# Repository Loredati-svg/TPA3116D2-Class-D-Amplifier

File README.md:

<h1 align="center">🔊 Class-D Stereo Audio Amplifier</h1>

An open-source stereo **Class-D** audio amplifier with a **USB-C digital input**, analog **bass / treble tone control** and a **volume knob**, built around the Texas Instruments **TPA3116D2** and designed in **KiCad 10.0**.

Plug a phone or a PC into the USB-C port: the board shows up as a standard USB sound card (no drivers needed) and drives a pair of passive bookshelf speakers (4–8 Ω) from a single **24 V DC** supply.

---

> 🛠️ **Project Status: Active Development (v1)**
> The v1 schematic is being finalized; PCB layout comes next. Suggestions and feedback are welcome!

> 📶 **About Bluetooth**
> Bluetooth support is currently **on hold**. It will be reintegrated in a future hardware revision, once the v1 board (USB-C, without Bluetooth) has been built and validated.

---

## Libraries

This project uses the shared KiCad libraries from L2-Hardware.

1. Clone the library repository **in the same parent folder as your project folders**, so that it sits next to them:

```bash
   git clone https://github.com/L2-Hardware/Kicad_Libs
```

   Expected folder structure:

```
   Kicad/
   ├── Kicad_Libs/
   ├── Project1/
   └── Project2/
   └── etc...
```
---

2. Inside the project folder, run the `bring_libs.bat` script to import the libraries into the project.

## 📋 Table of Contents
- [Technical Specifications](#-technical-specifications)
- [Signal Chain](#-signal-chain)
- [Circuit Blocks](#-circuit-blocks)
- [Gain Structure](#-gain-structure)
- [Repository Structure](#-repository-structure)
- [Manufacturing](#-manufacturing)
- [Roadmap](#-roadmap)
- [License](#-license)

---

## ⚡ Technical Specifications

| Parameter | Value |
| :--- | :--- |
| **Supply voltage** | 24 V DC (3–5 A recommended), 5.5 × 2.1 mm barrel jack |
| **Audio input** | USB-C (USB 2.0 Full-Speed, USB Audio Class 1.0), 16-bit / up to 48 kHz |
| **DAC** | Texas Instruments **PCM2704C** |
| **Tone control** | Active Baxandall – bass and treble, about ±12 dB |
| **Amplifier IC** | Texas Instruments **TPA3116D2** (stereo BTL, Master mode, 26 dB) |
| **Output power** | ≈ 2 × 40 W into 4 Ω (clean), up to 2 × 50 W at 10 % THD |
| **Speaker load** | 4–8 Ω passive speakers |
| **Speaker outputs** | Phoenix Contact MKDS 1,5/2-5,08 screw terminals |
| **Controls** | Bass, Treble, Volume (dual-gang potentiometers) |
| **PCB** | 4 layers, FR-4, 1.6 mm, 1 oz copper |

---

## 🔗 Signal Chain

```mermaid
flowchart LR
    A[Phone / PC<br/>USB-C] --> B[PCM2704C<br/>USB Audio DAC]
    B --> C[Baxandall tone control<br/>OPA1678 · Bass / Treble]
    C --> D[Volume<br/>dual log pot]
    D --> E[TPA3116D2<br/>26 dB]
    E --> F[LC filter]
    F --> G[Speakers<br/>4–8 Ω]
```

---

## 🧩 Circuit Blocks

### USB-C input and DAC
- USB 2.0 Type-C receptacle with **5.1 kΩ** pull-downs on CC1/CC2 (device / UFP), so the phone acts as host and supplies VBUS
- **USBLC6-2SC6** ESD protection on D+, D− and VBUS
- **PCM2704C** bus-powered from VBUS: USB Audio Class 1.0, driverless on Android, iOS, Windows, macOS and Linux
- 12 MHz crystal, 22 Ω series resistors and 1.5 kΩ pull-up on D+
- AC-coupled line outputs (10 µF + 47 kΩ)

### Tone control
- Active **Baxandall** network (one per channel) around a TI **OPA1678** (dual, rail-to-rail output, low noise)
- **Bass:** shelf centred around ≈ 50 Hz, tuned for deep 808-style bass
- **Treble:** ≈ 8–10 kHz, mainly to tame harsh highs
- Unity gain with the knobs centred

### Volume
- Dual-gang **A10K** logarithmic potentiometer
- Placed **after** the tone stage, so it also attenuates op-amp noise at low listening levels

### Analog supply
- **L78L12** LDO: 24 V → 12 V for the op-amp
- **VREF = 6 V** virtual ground (100 kΩ / 100 kΩ divider + 10 µF) for single-supply operation

### Power amplifier (TPA3116D2)
- **Gain / mode:** 20 kΩ to GND and 100 kΩ to GVDD on `GAIN/SLV` → Master mode, 26 dB, 30 kΩ input impedance
- **Inputs:** single-ended, negative inputs AC-grounded through capacitors matching the positive ones (3.3 µF)
- **Modulation:** BD mode, 400 kHz switching, no power limit
- **PVCC decoupling:** 1 nF + 100 nF ceramic + 220 µF + 470 µF low-ESR bulk on each side of the IC
- **Output filter:** 10 µH / 680 nF LC filter + RC snubbers for EMI
- **Protection:** `FAULTZ` tied to `SDZ` for automatic recovery after a fault
- **Thermal:** the DAD package has its **PowerPAD on top**, so a heatsink must be mounted on the IC

### Anti-pop
- The PCM2704C `SSPND` signal (high when USB audio is active) drives a **2N7002** inverter on the TPA3116D2 `MUTE` pin
- RC network on `MUTE` (100 kΩ + 4.7 µF): unmute ≈ 1 s after the DAC becomes active, mute within ≈ 0.1 s when the phone is unplugged, slew rate within datasheet limits
- RC delay on `SDZ` (100 kΩ + 10 µF) keeps the amplifier in shutdown while the supplies settle at power-up

### Front-panel controls

| Knob | Part | Function |
| :--- | :--- | :--- |
| **Bass** | B100K dual-gang (RV1) | Low-frequency boost / cut |
| **Treble** | B100K dual-gang (RV2) | High-frequency boost / cut |
| **Volume** | A10K dual-gang (RV3) | Master volume |

---

## 📊 Gain Structure

The gain chain is chosen so that **full volume reaches maximum clean power without clipping**, and the op-amp keeps headroom even with the bass knob fully up.

| Stage | Gain | Level at full scale |
| :--- | :--- | :--- |
| PCM2704C output | – | 0.64 Vrms |
| Tone control (flat) | ×1 (0 dB) | 0.64 Vrms |
| Volume (max) | ×1 | 0.64 Vrms |
| TPA3116D2 | ×20 (26 dB) | ≈ 12.8 Vrms → ≈ 40 W into 4 Ω |

Worst case (full-scale track, +12 dB bass boost): the OPA1678 output swings ≈ 7.2 Vpp around 6 V, well inside its 12 V rail-to-rail range. If the amplifier clips, it happens **after** the volume knob, so turning the volume down removes it.

---

## 📁 Repository Structure

```
Class-D-Bluetooth-5.0-Stereo-Audio-Amplifier/
├── KiCad_Project/
│   ├── Audio_Amp_v1/          # v1 – USB-C DAC + tone control (schematic + PCB)
│   └── Fabrication_files/     # Gerber, drill, BOM and CPL (coming soon)
├── libs/                           # Project-specific symbols, footprints and 3D models
└── README.md
```

### Schematic sheets

| Sheet | Content |
| :--- | :--- |
| `USB_DAC` | USB-C, ESD protection, PCM2704C, crystal, L78L12, power input, speaker terminals, anti-pop driver |
| `Tone_Volume_control` | OPA1678, VREF, Baxandall networks (L/R), volume potentiometer |
| `Power_Amplifier` | TPA3116D2, gain setting, PVCC decoupling, LC output filter, EMI snubbers |

---

## 🏭 Manufacturing

The board is designed to be manufactured by **JLCPCB** and assembled by hand (stencil + hot plate / hot air for SMD parts, soldering iron for through-hole parts).

| Option | Value |
| :--- | :--- |
| Layers | 4 |
| Thickness | 1.6 mm |
| Copper | 1 oz |
| Gerber export | Protel extensions, no X2 attributes |
| Drill | Excellon, mm, PTH + NPTH merged |
| Stencil | Top side only |

---

## 🗺️ Roadmap

**v1 – USB-C DAC (current)**
- [x] USB-C input and PCM2704C DAC
- [x] Baxandall tone control and volume
- [x] TPA3116D2 power stage
- [x] Anti-pop circuit
- [x] ERC and schematic review
- [x] PCB layout and DRC
- [ ] Fabrication, assembly and bring-up
- [ ] Measurements (frequency response, THD+N, noise)
- [ ] Enclosure and front panel

**Future**
- [ ] Bluetooth input (reintegrated once v1 is validated)

---

## 📜 License

This hardware project is released under the **CERN Open Hardware Licence Permissive v2 ([CERN-OHL-P v2](https://ohwr.org/cernohl))**.

<p align="center">Designed by <b>LOREDATI Circuits</b></p>

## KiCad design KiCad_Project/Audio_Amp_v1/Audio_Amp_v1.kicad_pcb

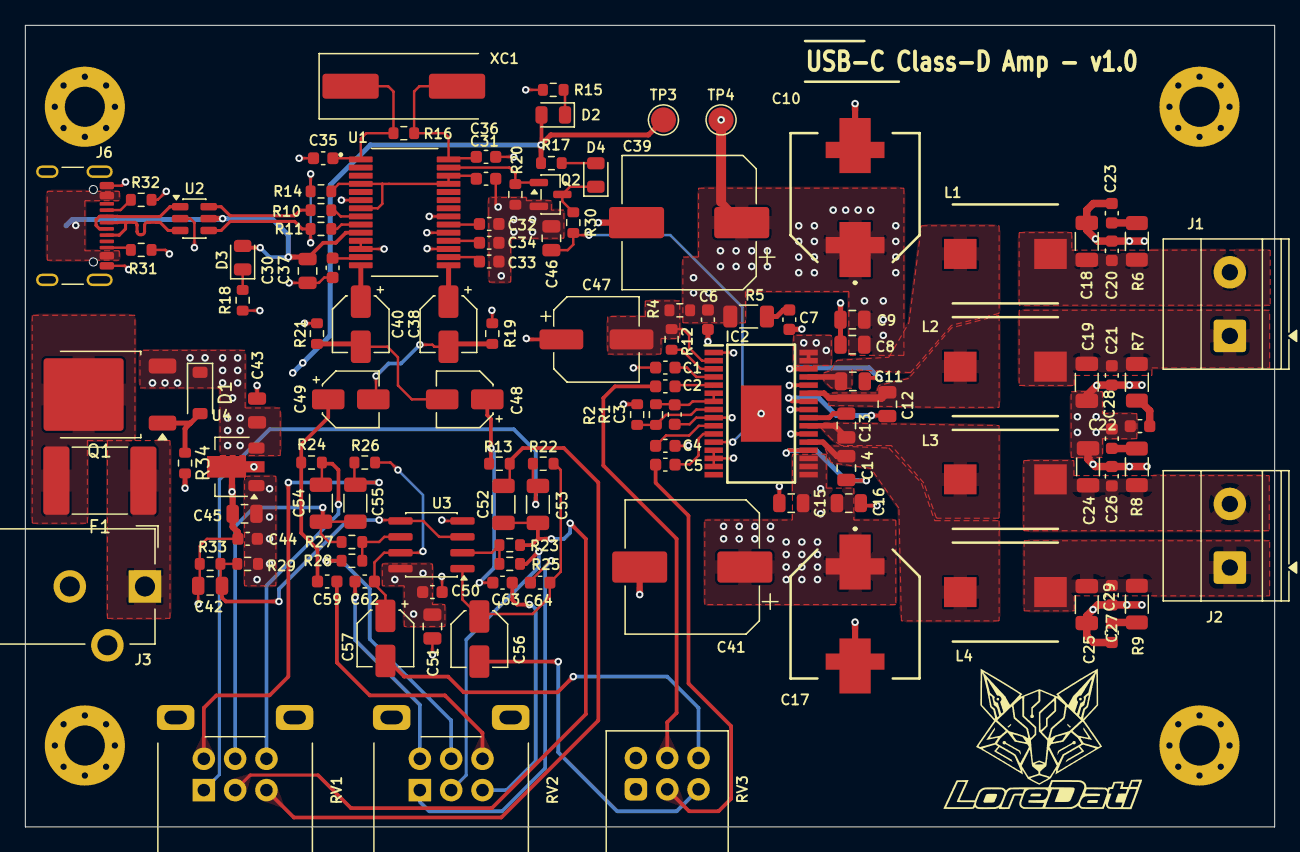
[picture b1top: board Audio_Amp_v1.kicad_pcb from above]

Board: 4 copper layers, 99.8 x 64.0 mm, 124 parts (0 on the bottom side), 80 nets.

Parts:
C1, C2, C4, C5: 3u3; C_0603_1608Metric
C3, C31, C32, C33, C37: 1u; C_0603_1608Metric
C6, C22, C23, C28, C29: 10n; C_0603_1608Metric
C7, C50: 100n; C_0603_1608Metric
C8, C15: 1n; C_0805_2012Metric
C9, C16: 100n; C_0805_2012Metric
C10, C17: 220u; EEHZT1E561UV
C11, C12, C13, C14: 220n; C_0805_2012Metric
C18, C19, C24, C25: 680n; C_1206_3216Metric
C20, C21, C26, C27: 1n; C_0603_1608Metric
C30, C42, C45, C51: 10u; C_0805_2012Metric
C34: 10u; C_0603_1608Metric
C35, C36: 33p; C_0603_1608Metric
C38, C40, C48, C49, C56, C57: 10u; CP_Elec_4x5.8
C39, C41: 470u; CP_Elec_10x10.5
C43: 0.33u; C_0805
C44: 0.1u; C_0603_1608Metric
C46: 4u7; C_0805_2012Metric
C47: 47u; CP_Elec_6.3x5.9
C52, C53, C54, C55: 100n; C_1206_3216Metric
C59, C62, C63, C64: 2n2; C_0603_1608Metric
D1: D_Zener; D_SOD-123
D2, D3, D4: LED; LED_0805_2012Metric
F1: Fuse; Fuse_2920_7451Metric_Pad2.10x5.45mm_HandSolder
H1, H2, H3, H4: MountingHole_Pad; MountingHole_3.2mm_M3_Pad_Via
IC2: TPA3116D2DAD; SOP65P810X120-32N
J1, J2: Screw_Terminal_01x02; TerminalBlock_Phoenix_MKDS-1,5-2-5.08_1x02_P5.08mm_Horizont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
J3: Barrel_Jack_Switch; BarrelJack_CUI_PJ-102AH_Horizontal
J6: USB_C_Receptacle_USB2.0_16P; USB_C_Receptacle_GCT_USB4105-xx-A_16P_TopMnt_Horizontal
L1, L2, L3, L4: 10u; INDPM8479X720N
Q1: Q_PMOS_GDS; TO-252-2
Q2: BSS138; SOT-23
R1, R4, R29, R30, R33: 100k; R_0603_1608Metric
R2: 20k; R_0603_1608Metric
R5, R6, R7, R8, R9: 3.3R; R_1206_3216Metric
R10, R11: 22; R_0603_1608Metric
R12, R18: 1k; R_0603_1608Metric
R13, R20, R22, R23, R24, R26, R27: 10k; R_0603_1608Metric
R14: 1.5k; R_0603_1608Metric
R15, R25, R28: 3k3; R_0603_1608Metric
R16: 1M; R_0603_1608Metric
R17, R19, R21, R34: 47k; R_0603_1608Metric
R31, R32: 5k1; R_0603_1608Metric
RV1, RV2: 100k; Potentiometer_Alps_RK09L_Double_Horizontal
RV3: 10k; Potentiometer_Alps_RK097_Dual_Horizontal
TP3, TP4: TestPoint; TestPoint_Pad_D2.0mm
U1: PCM2704CDB; SOP65P780X200-28N
U2: USBLC6-2SC6; SOT-23-6
U3: OPA1678IDR; SOIC-8_3.9x4.9mm_P1.27mm
U4: L78L12_SOT89; SOT-89-3
XC1: 12Mhz; Crystal_SMD_HC49-SD

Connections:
+12V: C44.1, C45.1, C50.1, C51.1, D2.2 (A), R17.2, R29.2, TP3.1 (1_1), U3.8 (V+), U4.1 (OUT)
+24V: C6.2, C8.1, C9.1, C10.1, C15.1, C16.1, C17.1, C39.1, C41.1, C43.1, D1.1 (K), IC2.17 (AVCC), IC2.18 (PVCC_1), IC2.19 (PVCC_2), IC2.31 (PVCC_3), IC2.32 (PVCC_4), Q1.3 (S), R4.1, R5.1, TP4.1 (1_1), U4.3 (IN)
+24VIN: F1.1, J3.1
/Tone-Volume_control/VREF: C42.1, R29.1, R33.2, U3.3 (+), U3.5 (+)
/USB_DAC/DAC_ACTIVE: Q2.1 (G), R20.2, U1.27 (~SSPND)
/USB_DAC/DAC_D+: R11.2, U1.9 (D+)
/USB_DAC/DAC_D-: R10.2, U1.8 (D-)
/USB_DAC/ESD_D+: R11.1, R14.2, U2.4 (I/O2)
/USB_DAC/ESD_D-: R10.1, U2.6 (I/O1)
/USB_DAC/USB_D+: J6.A6 (D+), J6.B6 (D+), U2.3 (I/O2)
/USB_DAC/USB_D-: J6.A7 (D-), J6.B7 (D-), U2.1 (I/O1)
DAC_L: C40.2, C48.2, R21.2
DAC_R: C38.2, C49.2, R19.2
GNDA: C1.1, C3.1, C4.2, C6.1, C7.1, C8.2, C9.2, C10.2, C15.2, C16.2, C17.2, C18.2, C19.1, C20.2, C21.1, C22.1, C23.2, C24.2, C25.1, C26.2, C27.1, C28.2, C29.1, C30.1, C31.2, C32.1, C33.1, C34.1, C35.1, C36.1, C37.2, C39.2, C41.2, C42.2, C43.2, C44.2, C45.2, C46.2, C47.1, C50.2, C51.2, H1.1 (1_1), H2.1 (1_1), H3.1 (1_1), H4.1 (1_1), IC2.1 (MODSEL), IC2.9 (GND_1), IC2.13 (AM2), IC2.14 (AM1), IC2.15 (AM0), IC2.22 (GND_2), IC2.25 (GND_3), IC2.28 (GND_4), IC2.33 (GND), J3.2, J3.3, J6.A1 (GND), J6.A12 (GND), J6.B1 (GND), J6.B12 (GND), J6.SH (SHIELD), Q2.2 (S), R2.2, R15.2, R18.2, R19.1, R20.1, R21.1, R31.2, R32.2, R33.1, R34.2, RV1.MP (GNDA), RV2.MP (GNDA), RV3.1, RV3.4, U1.6 (DGND), U1.11 (ZGND), U1.12 (AGNDL), U1.17 (AGNDR), U1.19 (PGND), U1.21 (HOST), U2.2 (GND), U3.4 (V-), U4.2 (GND)
IN_P_LEFT: C5.2, RV3.2
IN_P_RIGHT: C2.1, RV3.5
MUTE: C46.1, IC2.12 (MUTE), R30.1
unnamed: C7.2, R5.2
unnamed: C22.2, R7.1
unnamed: C23.1, R6.2
unnamed: C28.1, R8.2
unnamed: C29.2, R9.1
unnamed: C48.1, C63.2, R13.1
unnamed: C49.1, C59.2, R24.1
unnamed: C52.1, C53.1, R23.2, RV1.2
unnamed: C52.2, R13.2, RV1.3
unnamed: C53.2, R22.1, RV1.1
unnamed: C54.1, C55.1, R27.2, RV1.5
unnamed: C54.2, R24.2, RV1.6
unnamed: C55.2, R26.1, RV1.4
unnamed: C56.1, C64.1, R22.2, U3.1
unnamed: C56.2, RV3.3
unnamed: C57.1, C62.1, R26.2, U3.7
unnamed: C57.2, RV3.6
unnamed: C59.1, RV2.6
unnamed: C62.2, RV2.4
unnamed: C63.1, RV2.3
unnamed: C64.2, RV2.1
unnamed: D1.2 (A), Q1.1 (G), R34.1
unnamed: D2.1 (K), R15.1
unnamed: D3.1 (K), R18.1
unnamed: D4.2 (A), R17.1
unnamed: D4.1 (K), Q2.3 (D), R30.2
unnamed: C14.1, IC2.20 (BSNL)
unnamed: C12.1, IC2.26 (BSNR)
unnamed: C13.1, IC2.24 (BSPL)
unnamed: C11.1, IC2.30 (BSPR)
unnamed: IC2.3 (FAULTZ), R12.2
unnamed: IC2.8 (GAIN/SLV), R1.2, R2.1
unnamed: C3.2, IC2.6 (PLIMIT), IC2.7 (GVDD), R1.1
unnamed: C5.1, IC2.11 (LINN)
unnamed: C4.1, IC2.10 (LINP)
unnamed: C14.2, IC2.21 (OUTNL), L4.1
unnamed: C12.2, IC2.27 (OUTNR), L2.2
unnamed: C13.2, IC2.23 (OUTPL), L3.1
unnamed: C11.2, IC2.29 (OUTPR), L1.1
unnamed: C2.2, IC2.5 (RINN)
unnamed: C1.2, IC2.4 (RINP)
unnamed: C47.2, IC2.2 (SDZ), R4.2, R12.1
unnamed: J6.A5 (CC1), R32.1
unnamed: J6.B5 (CC2), R31.1
unnamed: F1.2, Q1.2 (D)
unnamed: R25.1, RV2.2
unnamed: R28.1, RV2.5
unnamed: C31.1, R14.1, U1.4 (PSEL), U1.7 (VDD), U1.25 (TEST1), U1.26 (TEST0)
unnamed: C37.1, U1.13 (VCCL)
unnamed: C32.2, U1.20 (VCCP)
unnamed: C33.2, U1.16 (VCCR)
unnamed: C34.2, U1.18 (VCOM)
unnamed: C40.1, U1.14 (VOUTL)
unnamed: C38.1, U1.15 (VOUTR)
unnamed: C36.2, R16.2, U1.28 (XTI), XC1.2
unnamed: C35.2, R16.1, U1.1 (XTO), XC1.1
unnamed: R23.1, R25.2, U3.2 (-)
unnamed: R27.1, R28.2, U3.6 (-)
OUT_N_LEFT: C25.2, C27.2, J2.1, L4.2, R9.2
OUT_N_RIGHT: C19.2, C21.2, J1.1, L2.1, R7.2
OUT_P_LEFT: C24.1, C26.1, J2.2, L3.2, R8.1
OUT_P_RIGHT: C18.1, C20.1, J1.2, L1.2, R6.1
VBUS: C30.2, D3.2 (A), J6.A4 (VBUS), J6.A9 (VBUS), J6.B4 (VBUS), J6.B9 (VBUS), U1.10 (VBUS), U2.5 (VBUS)

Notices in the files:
README.md:
License: CERN-OHL-P
